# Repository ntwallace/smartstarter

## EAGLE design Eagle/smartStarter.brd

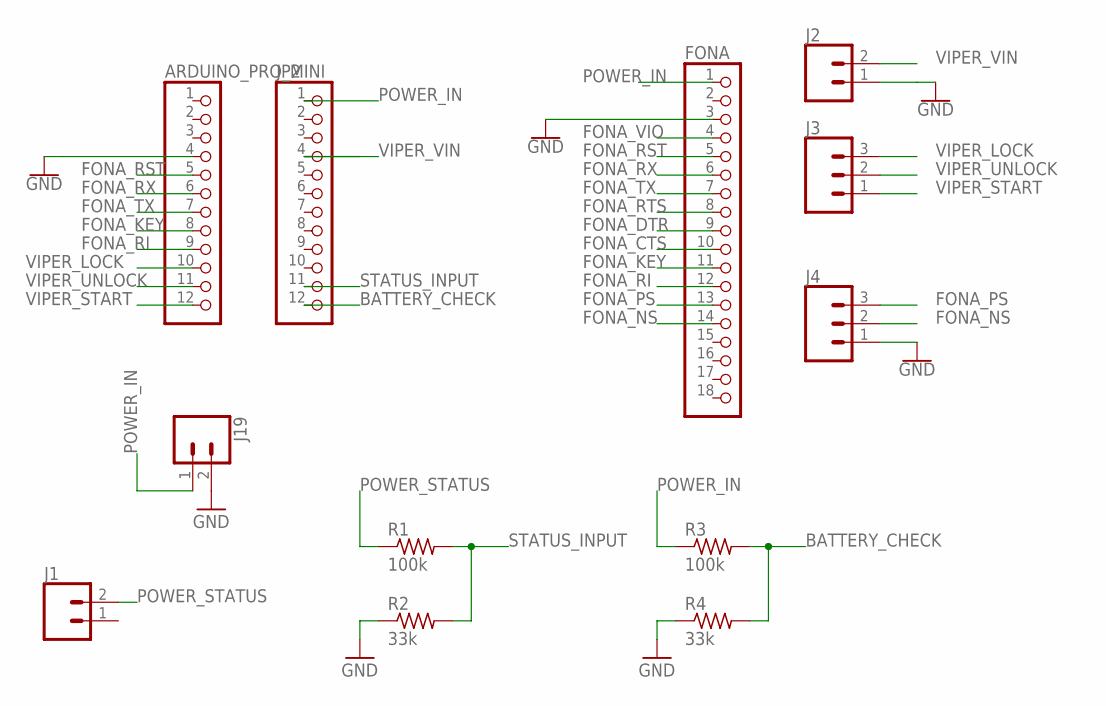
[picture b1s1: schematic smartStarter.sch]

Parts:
ARDUINO_PRO_MINI: PINHD-1X12; 1X12
FONA: PINHD-1X18; 1X18
J1, J2, J19: CONN_023.5MM; SCREWTERMINAL-3.5MM-2
J3, J4: CONN_03SCREW; SCREWTERMINAL-3.5MM-3
JP2: PINHD-1X12; 1X12
R1, R3: 100k; 0204/7
R2, R4: 33k; 0204/7

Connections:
BATTERY_CHECK: JP2.12, R3.2, R4.2
FONA_CTS: FONA.10
FONA_DTR: FONA.9
FONA_KEY: ARDUINO_PRO_MINI.8, FONA.11
FONA_NS: FONA.14, J4.2
FONA_PS: FONA.13, J4.3
FONA_RI: ARDUINO_PRO_MINI.9, FONA.12
FONA_RST: ARDUINO_PRO_MINI.5, FONA.5
FONA_RTS: FONA.8
FONA_RX: ARDUINO_PRO_MINI.6, FONA.6
FONA_TX: ARDUINO_PRO_MINI.7, FONA.7
FONA_VIO: FONA.4
GND: ARDUINO_PRO_MINI.4, FONA.3, J2.1, J4.1, J19.2, R2.1, R4.1
POWER_IN: FONA.1, J19.1, JP2.1, R3.1
POWER_STATUS: J1.2, R1.1
STATUS_INPUT: JP2.11, R1.2, R2.2
VIPER_LOCK: ARDUINO_PRO_MINI.10, J3.3
VIPER_START: ARDUINO_PRO_MINI.12, J3.1
VIPER_UNLOCK: ARDUINO_PRO_MINI.11, J3.2
VIPER_VIN: J2.2, JP2.4

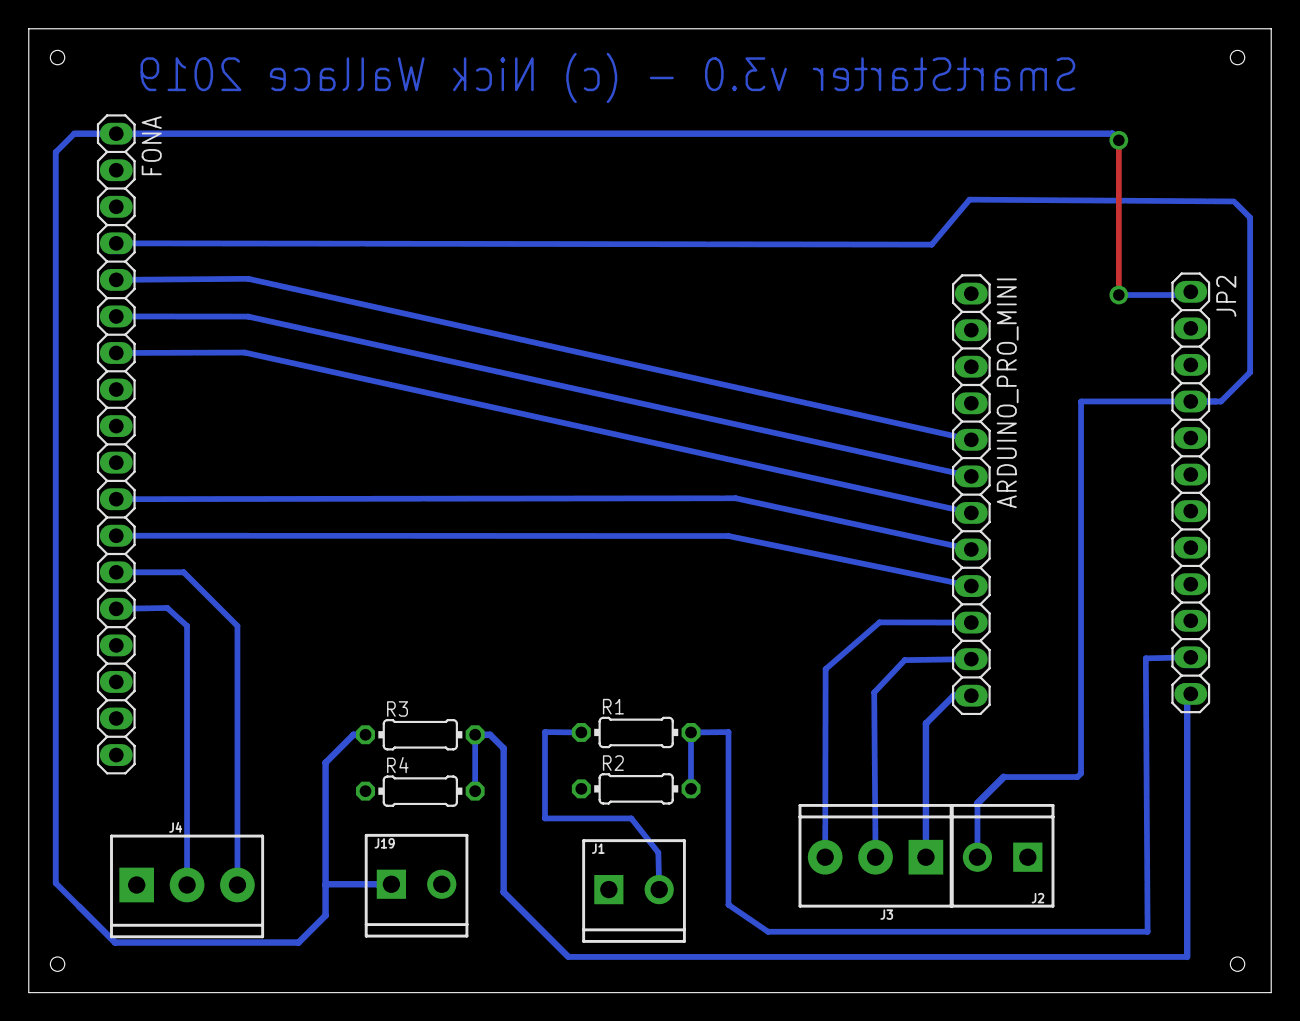
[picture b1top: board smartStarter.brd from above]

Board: 2 copper layers, 86.3 x 67.0 mm, 12 parts (0 on the bottom side), 16 nets.

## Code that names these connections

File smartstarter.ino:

// add libs
#include <SoftwareSerial.h>
#include <Adafruit_FONA.h>
#include <avr/wdt.h>
#include <avr/sleep.h>
#include <avr/power.h>
#include <avr/interrupt.h>

// define FONA pins
#define FONA_RX 2
#define FONA_TX 3
#define FONA_RST 4
#define FONA_RI 5
#define FONA_KEY 10
#define FONA_BATTERY 11
#define MOSFET 12

// define keyfob i/o
#define LOCK_PIN 6
#define UNLOCK_PIN 7
#define REMOTE_PIN 8
#define POWER_STATUS_PIN 9
#define LOCK true
#define UNLOCK false

// initialize battery vars
int lastBatteryPcnt = 0;
int batteryBasement = 000;  // lowest voltage allowed on numberic scale 0-1023, ex. 500
float batteryConstant = 100.0 / (1023 - batteryBasement);
boolean chargeBattery = false;

// initialize SMS vars
char sender[25]; // stores sender SMS #
char replybuffer[255]; // buffer for replies
uint8_t readline(char *buff, uint8_t maxbuff, uint16_t timeout = 0);
int8_t lastsmsnum = 0;

boolean powerOn = false;

// initialize FONA software serial
SoftwareSerial fonaSS = SoftwareSerial(FONA_TX, FONA_RX);
Adafruit_FONA_3G fona = Adafruit_FONA_3G(FONA_RST);

boolean checkBattery(int batteryVal) {
  int batteryPcnt = (batteryVal - batteryBasement) * batteryConstant;

  if (lastBatteryPcnt != batteryPcnt) {
    Serial.print("Battery @ ");
    Serial.print(batteryPcnt);
    Serial.print("%");
    Serial.println();
    lastBatteryPcnt = batteryPcnt;
  }

  if (batteryPcnt <= 40) {  //battery at or below 40%
    return true;
  } else {
    return false;
  }
}

boolean fonainit(void) {
  // power the FONA on
  pinMode(FONA_KEY, OUTPUT);
  digitalWrite(FONA_KEY, LOW);
  delay(3000);
  pinMode(FONA_KEY, INPUT);

  while (!Serial);

  fonaSS.begin(4800);
  Serial.println(F("Initializing...."));

  if (! fona.begin(fonaSS)) {
    Serial.println(F("Couldn't find FONA"));
    return false;
  }
  Serial.println(F("FONA is OK"));
  return true;

}

// setup watchdog function && sleep
int nbrRemaining;
void configure_wdt(void) {
  cli();                           // disable interrupts for changing the registers

  MCUSR = 0;                       // reset status register flags
  WDTCSR |= 0b00011000;            // Set WDCE (5th from left) and WDE (4th from left) to enter config
  WDTCSR =  0b01000000 | 0b100001; // set WDIE/clear WDE | set to 8 sec intervals

  sei();                           // re-enable interrupts
}

// setup watchdog interrupt
ISR(WDT_vect) {
  wdt_disable();  // disable watchdog
}

void sleep(int ncycles) {
  nbrRemaining = (ncycles / 8); // defines how many cycles should sleep

  // Set sleep to full power down
  set_sleep_mode(SLEEP_MODE_PWR_DOWN);

  // Turn off the ADC while asleep.
  power_adc_disable();

  while (nbrRemaining > 0) { // while some cycles left, sleep!
    // Enable sleep and enter sleep mode.
    sleep_mode();

    // When awake, disable sleep mode
    sleep_disable();

    // we have slept one time more
    nbrRemaining = nbrRemaining - 1;
  }

  // put everything on again
  power_all_enable();
}

void setup() {
  // set keyfob pins off
  pinMode(LOCK_PIN, INPUT);
  pinMode(UNLOCK_PIN, INPUT);
  pinMode(REMOTE_PIN, INPUT);

  // setup car power status pin
  pinMode(POWER_STATUS_PIN, INPUT);

  // initialize FONA
  Serial.begin(115200);
  while (! fonainit()) {
    delay(5000);
  }

  // get battery status, charge if =< 40%
  chargeBattery = checkBattery(analogRead(FONA_BATTERY));

  pinMode(FONA_RI, INPUT);
  digitalWrite(FONA_RI, HIGH); // turn on pullup on RI
  // turn on RI pin change on incoming SMS!
  fona.sendCheckReply(F("AT+CFGRI=1"), F("OK"));
}

void loop() {
  while (fona.getNetworkStatus() != 1) {
    Serial.println("Waiting for cell connection");
    delay(6000);
  }

  // Check if the interrupt pin went low, break out to check manually for SMS, and connection status
  for (uint16_t i = 0; i < 5000; i++) {
    if (! digitalRead(FONA_RI)) {
      // RI pin went low, SMS received?
      Serial.println(F("RI interrupt went low"));
      break;
    }
    delay(1);
  }

  int8_t smsnum = fona.getNumSMS();
  /* if (smsnum < 0) {
    Serial.println(F("Could not read # SMS"));
    return;
    } else {
    Serial.print(smsnum); Serial.println(F(" SMS on SIM card!"));
    } */

  if (smsnum == 0) return;
  /*if (smsnum == 0 && !chargeBattery) {
  digitalWrite(FONA_KEY, LOW);
  delay(3000);
  sleep(72); // sleep for 72 sec */

  // SMS was found
  uint8_t n = 0;
  while (true) {
    uint16_t smslen;

    uint8_t len = fona.readSMS(n, replybuffer, 250, &smslen); // pass in buffer and max len!
    // if the length is zero, its a special case where the index number is higher
    // so increase the max we'll look at!
    if (len == 0) {
      Serial.println(F("[empty slot]"));
      n++;
      continue;
    }
    if (! fona.getSMSSender(n, sender, sizeof(sender))) {
      // failed to get the sender?
      sender[0] = 0;
    }

    Serial.print(F("***** SMS #")); Serial.print(n);
    Serial.print(" ("); Serial.print(len); Serial.println(F(") bytes *****"));
    Serial.println(replybuffer);
    Serial.print(F("From: ")); Serial.println(sender);
    Serial.println(F("*****"));

    if (strcasecmp(replybuffer, "lock") == 0) {
      doors(LOCK); // lock the doors
    }
    if (strcasecmp(replybuffer, "unlock") == 0) {
      doors(UNLOCK); // unlock the doors
    }
    if (strcasecmp(replybuffer, "remote") == 0) {
      remote(); // start or stop car
    }

    delay(1000);
    break;
  }
  fona.deleteSMS(n);

  delay(1000);
}

void doors(boolean locked) {
  if (locked) {
    // power to lock button on keyfob
    pinMode(LOCK_PIN, OUTPUT);
    digitalWrite(LOCK_PIN, LOW);
    delay(1000);
    pinMode(LOCK_PIN, INPUT);

    Serial.println("Attemped to lock doors");
    Serial.print("Attempting to send SMS to: "); Serial.println(sender);
    sms(sender, "Door lock signal sent!");

  } else {
    //power to unlock button on keyfob
    pinMode(UNLOCK_PIN, OUTPUT);
    digitalWrite(UNLOCK_PIN, LOW);
    delay(1000);
    pinMode(UNLOCK_PIN, INPUT);

    Serial.println("Attemped to unlock doors");
    Serial.print("Attempting to send SMS to: "); Serial.println(sender);
    sms(sender, "Door unlock signal sent!");
  }
}

void remote() {
  // if no 5v car power to status pin, car is off
  powerOn = digitalRead(POWER_STATUS_PIN) == HIGH;

  // power remote start/stop button on keyfob
  pinMode(REMOTE_PIN, OUTPUT);
  digitalWrite(REMOTE_PIN, LOW);
  delay(1000);
  pinMode(REMOTE_PIN, INPUT);

  Serial.println("Attempted to turn car on/off!");
  sms(sender, "Attempted to turn car on/off!");
  delay(5000);

  // check 5v line status has changed after button was powered
  if (!digitalRead(POWER_STATUS_PIN) && powerOn ) { // car was previously on, now off
    Serial.println("Car was turned off!");
    sms(sender, "Car was turned off!");
    powerOn = false;
  }
  else if (digitalRead(POWER_STATUS_PIN) && !powerOn) { // car was previously off, now on
    Serial.println("Car was turned on!");
    sms(sender, "Car was turned on!");
    powerOn = true;
  }
  else if ((digitalRead(POWER_STATUS_PIN) && powerOn) || (!digitalRead(POWER_STATUS_PIN) && !powerOn)) { // car state didn't change
    Serial.println("Remote start/stop failed!");
    sms(sender, "Remote start/stop failed!");
  }

}

void sms(char sender[10], char message[25]) {
  flushSerial();
  if (!fona.sendSMS(sender, message)) {
    Serial.println(F("Failed"));
  } else {
    Serial.print(F("Sent SMS response to: ")); Serial.println(sender);
  }
}

void flushSerial() {
  while (Serial.available())
    Serial.read();
}

void softReset() {
  asm volatile ("  jmp 0");
}

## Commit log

2018-04-04 Updated sketch to v3
2019-03-04 Update success response, add Eagle files

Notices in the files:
parts and their libraries:
SparkFun-Connectors: Licensing: Creative Commons ShareAlike 4.0 International - https://creativecommons.org/licenses/by-sa/4.0
